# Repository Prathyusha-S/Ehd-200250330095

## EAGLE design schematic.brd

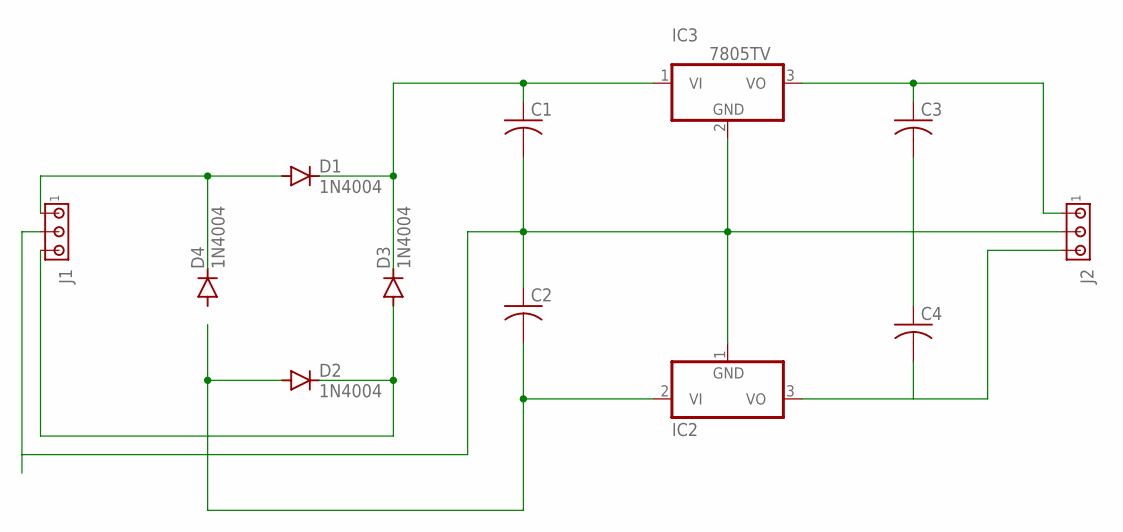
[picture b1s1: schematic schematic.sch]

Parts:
C1, C2, C3, C4: C-US102-064X133; C102-064X133
D1, D2, D3, D4: 1N4004; DO41-10
IC2: 7908T; TO220H
IC3: 7805TV; TO220V
J1, J2: MTA03-100; 10X03MTA

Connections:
unnamed: D1.A, D4.C, J1.1
unnamed: C2.2, D2.A, IC2.2 (VI)
unnamed: D2.C, D3.A, J1.3
unnamed: C1.1, D1.C, D3.C, IC3.1 (VI)
unnamed: C1.2, C2.1, IC2.1 (GND), IC3.2 (GND), J1.2, J2.2
unnamed: C3.1, IC3.3 (VO), J2.1
unnamed: C3.2, C4.1
unnamed: IC2.3 (VO), J2.3

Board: 2 copper layers, 12 parts (0 on the bottom side), 8 nets, no tracks yet.

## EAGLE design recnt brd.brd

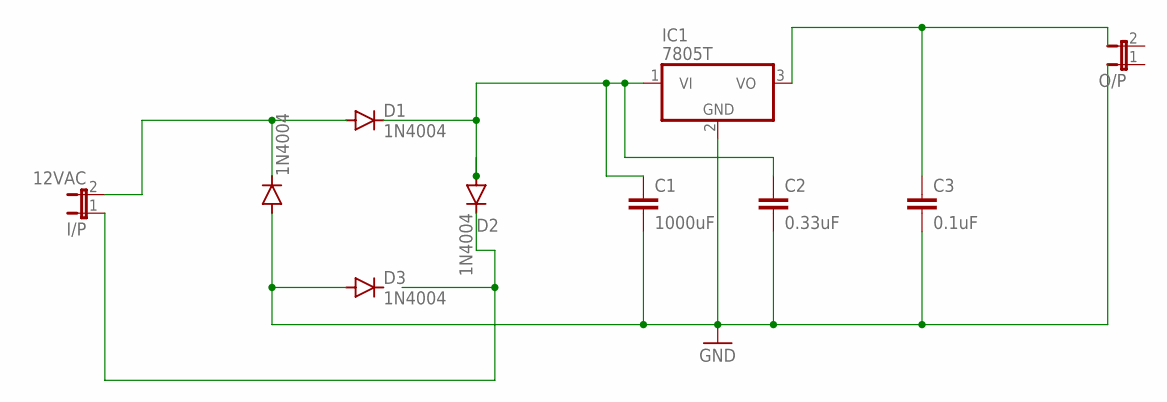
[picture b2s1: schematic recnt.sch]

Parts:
C1: 1000uF; C2.5-3
C2: 0.33uF; C2.5-3
C3: 0.1uF; C2.5-3
D1, D2, D3, D4: 1N4004; DO41-10
I/P: 12VAC; JP1
IC1: 7805T; TO220H
O/P: JP1E; JP1

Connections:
D2: D2.C, I/P.1
GND: C1.2, C2.2, C3.2, D3.A, D4.A, IC1.2 (GND)
unnamed: D1.A, D4.C, I/P.2
unnamed: C1.1, C2.1, D1.C, D2.A, IC1.1 (VI)
unnamed: C3.1, IC1.3 (VO)

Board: 2 copper layers, 10 parts (0 on the bottom side), 5 nets, no tracks yet.
